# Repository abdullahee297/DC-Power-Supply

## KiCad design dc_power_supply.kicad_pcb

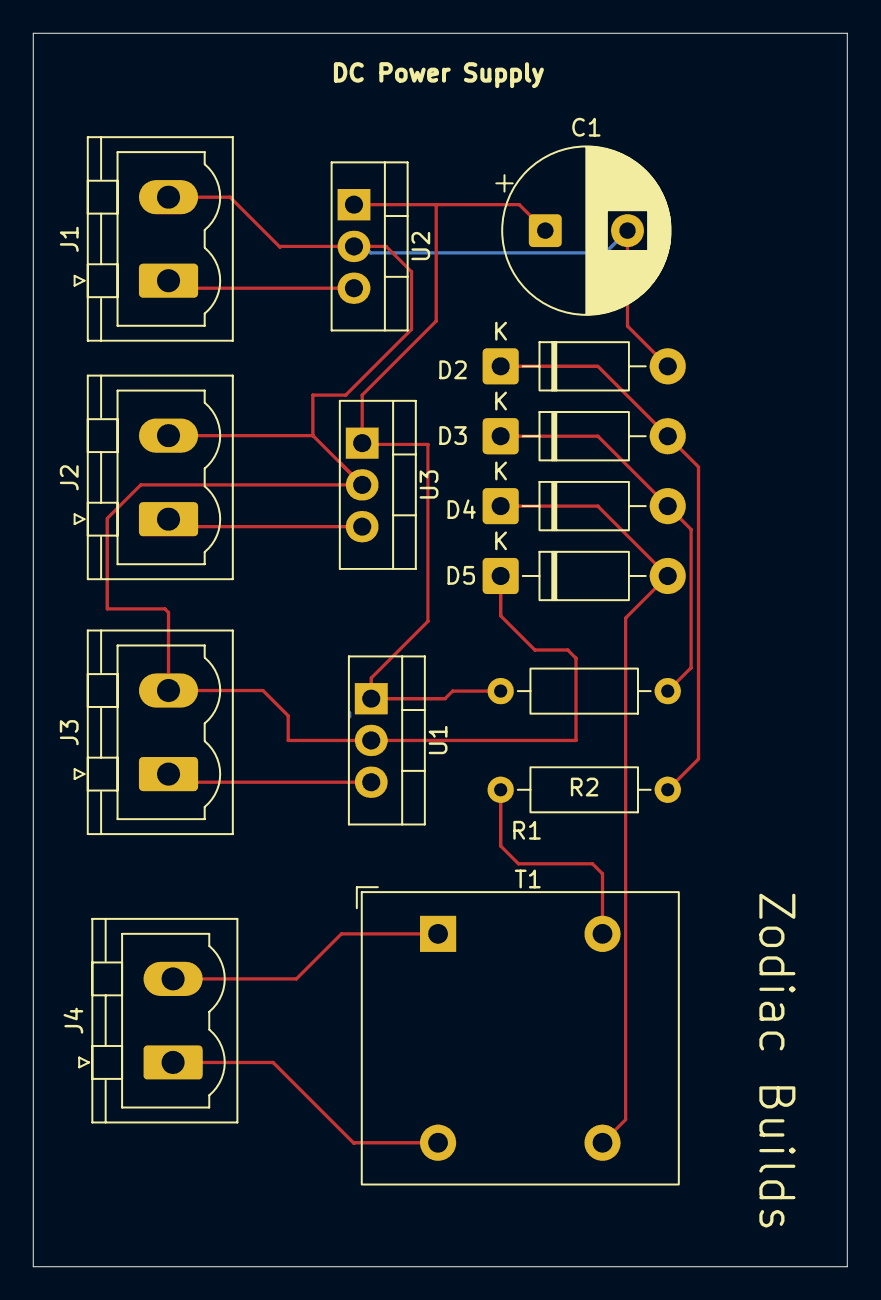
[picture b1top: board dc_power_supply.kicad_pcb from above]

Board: 2 copper layers, 49.5 x 75.0 mm, 15 parts (0 on the bottom side), 11 nets.

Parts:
C1: 100uF; CP_Radial_D10.0mm_P5.00mm
D2, D3, D4, D5: 1N4005; D_DO-41_SOD81_P10.16mm_Horizontal
J1: PhoenixContact_MSTBVA_2,5_2-G-5,08_1x02_P5.08mm_Vertical
J2, J3, J4: Conn_01x02_Socket; PhoenixContact_MSTBVA_2,5_2-G-5,08_1x02_P5.08mm_Vertical
R1: 1k; R_Axial_DIN0207_L6.3mm_D2.5mm_P10.16mm_Horizontal
R2: 330; R_Axial_DIN0207_L6.3mm_D2.5mm_P10.16mm_Horizontal
T1: Transformer; Transformer_Zeming_ZMPT101K
U1: LM7812_TO220; TO-220-3_Vertical
U2: LM7805_TO220; TO-220-3_Vertical
U3: LM7809_TO220; TO-220-3_Vertical

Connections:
/12V: C1.1, R2.2, U1.1 (VI), U2.1 (VI), U3.1 (VI)
GND: C1.2, D2.2 (A), D5.1 (K), J1.2, J2.2, J3.2, U1.2 (GND), U2.2 (GND), U3.2 (GND)
unnamed: D2.1 (K), D3.2 (A), R1.1
unnamed: D3.1 (K), D4.2 (A), R2.1
unnamed: D4.1 (K), D5.2 (A), T1.3 (SA)
unnamed: J1.1, U2.3 (VO)
unnamed: J2.1, U3.3 (VO)
unnamed: J3.1, U1.3 (VO)
unnamed: J4.1, T1.2 (AB)
unnamed: J4.2, T1.1 (AA)
unnamed: R1.2, T1.4 (SB)
